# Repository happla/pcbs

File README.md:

# pcbs
## Links:
[ESP32-C3-Dev-board without  filling and gnd plane](https://github.com/happla/pcbs/tree/main/xiaobreakout) 
<br>

# enclosure

## Links : 
[ILI9341 display enclosure v1](https://github.com/happla/pcbs/tree/main/enclosure/ili9341case)
<br>

final version of ili9341 display case for iot project. V3 with m3 screw and m16x2 cable gland placeholders <br>

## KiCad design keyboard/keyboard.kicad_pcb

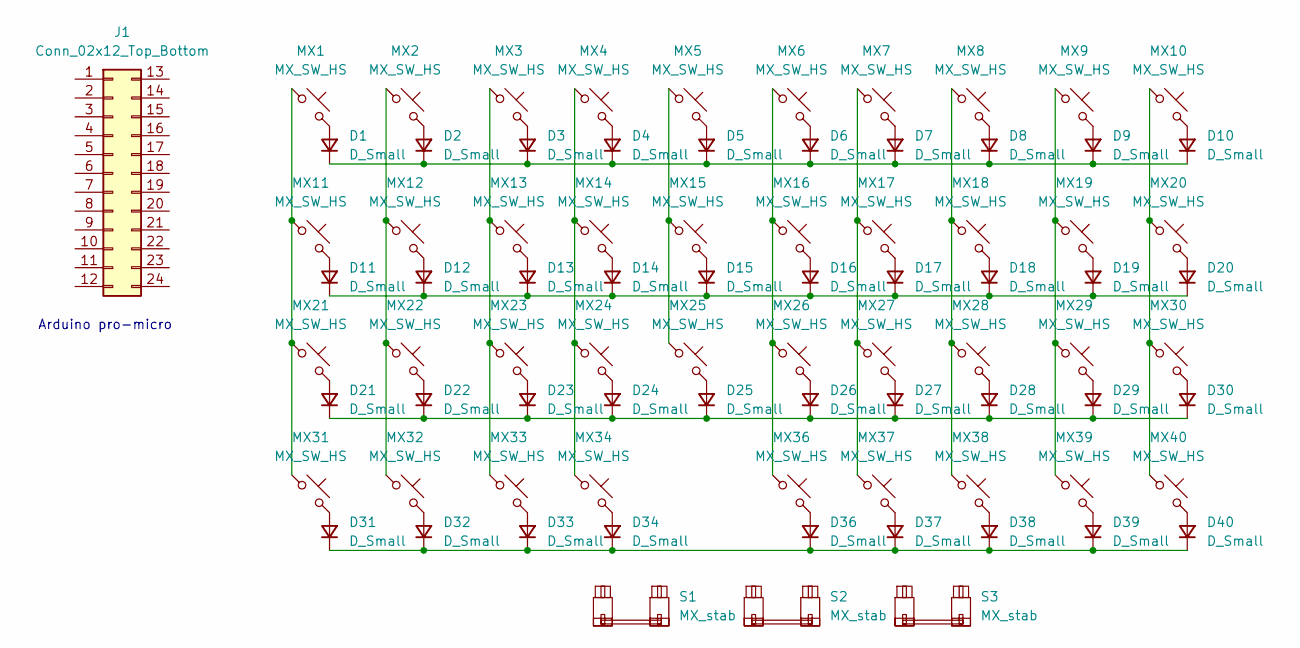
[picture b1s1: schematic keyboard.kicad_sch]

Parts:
D1, D2, D3, D4, D5, D6, D7, D8, D9, D10, D11, D12, D13, D14, D15, D16, D17, D18, D19, D20, D21, D22, D23, D24, D25, D26, D27, D28, D29, D30, D31, D32, D33, D34, D36, D37, D38, D39, D40: D_Small; D_SOD-123
J1: Conn_02x12_Top_Bottom; ProMicro_USBup
MX1, MX2, MX3, MX4, MX5, MX6, MX7, MX8, MX9, MX12, MX13, MX14, MX15, MX16, MX17, MX18, MX19, MX22, MX23, MX24, MX25, MX26, MX27, MX28, MX29, MX31, MX32, MX33, MX34, MX36, MX37, MX38, MX39: MX_SW_HS; SW_MX_1u
MX10, MX21: MX_SW_HS; SW_MX_1.75u
MX11, MX30: MX_SW_HS; SW_MX_1.25u
MX20, MX40: MX_SW_HS; SW_MX_1.5u
S1: MX_stab; STAB_MX_P_2u
S2: MX_stab; STAB_MX_P_2.25u
S3: MX_stab; STAB_MX_6.25u

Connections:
unnamed: D1.2 (A), MX1.2
unnamed: D1.1 (K), D2.1 (K), D3.1 (K), D4.1 (K), D5.1 (K), D6.1 (K), D7.1 (K), D8.1 (K), D9.1 (K), D10.1 (K)
unnamed: D2.2 (A), MX2.2
unnamed: D3.2 (A), MX3.2
unnamed: D4.2 (A), MX4.2
unnamed: D5.2 (A), MX5.2
unnamed: D6.2 (A), MX6.2
unnamed: D7.2 (A), MX7.2
unnamed: D8.2 (A), MX8.2
unnamed: D9.2 (A), MX9.2
unnamed: D10.2 (A), MX10.2
unnamed: D11.2 (A), MX11.2
unnamed: D11.1 (K), D12.1 (K), D13.1 (K), D14.1 (K), D15.1 (K), D16.1 (K), D17.1 (K), D18.1 (K), D19.1 (K), D20.1 (K)
unnamed: D12.2 (A), MX12.2
unnamed: D13.2 (A), MX13.2
unnamed: D14.2 (A), MX14.2
unnamed: D15.2 (A), MX15.2
unnamed: D16.2 (A), MX16.2
unnamed: D17.2 (A), MX17.2
unnamed: D18.2 (A), MX18.2
unnamed: D19.2 (A), MX19.2
unnamed: D20.2 (A), MX20.2
unnamed: D21.2 (A), MX21.2
unnamed: D21.1 (K), D22.1 (K), D23.1 (K), D24.1 (K), D25.1 (K), D26.1 (K), D27.1 (K), D28.1 (K), D29.1 (K), D30.1 (K)
unnamed: D22.2 (A), MX22.2
unnamed: D23.2 (A), MX23.2
unnamed: D24.2 (A), MX24.2
unnamed: D25.2 (A), MX25.2
unnamed: D26.2 (A), MX26.2
unnamed: D27.2 (A), MX27.2
unnamed: D28.2 (A), MX28.2
unnamed: D29.2 (A), MX29.2
unnamed: D30.2 (A), MX30.2
unnamed: D31.2 (A), MX31.2
unnamed: D31.1 (K), D32.1 (K), D33.1 (K), D34.1 (K), D36.1 (K), D37.1 (K), D38.1 (K), D39.1 (K), D40.1 (K)
unnamed: D32.2 (A), MX32.2
unnamed: D33.2 (A), MX33.2
unnamed: D34.2 (A), MX34.2
unnamed: D36.2 (A), MX36.2
unnamed: D37.2 (A), MX37.2
unnamed: D38.2 (A), MX38.2
unnamed: D39.2 (A), MX39.2
unnamed: D40.2 (A), MX40.2
unnamed: MX1.1, MX11.1, MX21.1, MX31.1
unnamed: MX10.1, MX20.1, MX30.1, MX40.1
unnamed: MX2.1, MX12.1, MX22.1, MX32.1
unnamed: MX3.1, MX13.1, MX23.1, MX33.1
unnamed: MX4.1, MX14.1, MX24.1, MX34.1
unnamed: MX5.1, MX15.1, MX25.1
unnamed: MX6.1, MX16.1, MX26.1, MX36.1
unnamed: MX7.1, MX17.1, MX27.1, MX37.1
unnamed: MX8.1, MX18.1, MX28.1, MX38.1
unnamed: MX9.1, MX19.1, MX29.1, MX39.1

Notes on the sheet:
Arduino pro-micro

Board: 2 copper layers, 82 parts (0 on the bottom side), 53 nets, no tracks yet.

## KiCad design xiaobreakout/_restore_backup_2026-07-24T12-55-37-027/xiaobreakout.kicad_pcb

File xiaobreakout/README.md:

# ESP32-C3 BLE Development Board

> **Status:** Work in Progress (Incomplete and untested)

A custom, ultra-compact devboard designed specifically for a Bluetooth Low Energy (BLE) project.

## Specifications

* **MCU:** ESP32-C3
* **PCB Size:** ~30 x 25 mm
* **Connectivity:** JST connectors or standard female Dupont headers

## Pin Connections

* **I2C:** [Add specific GPIOs, e.g., SDA: GPIO4, SCL: GPIO5]
* **Battery:** [Add power input details]
* **Joystick:** [Add pin mapping]
* **SW1:** [Add button pin]

## PCB Preview

## Next Steps

* [ ] Implement a circuit/method to accurately measure low-power consumption.
* [ ] Expand pin breakouts and connections for more universal prototyping use.
* [ ] Explore designing a completely scratch-built revision using an alternative MCU (like a Nordic nRF chip or CH32) to benchmark minimal power consumption.

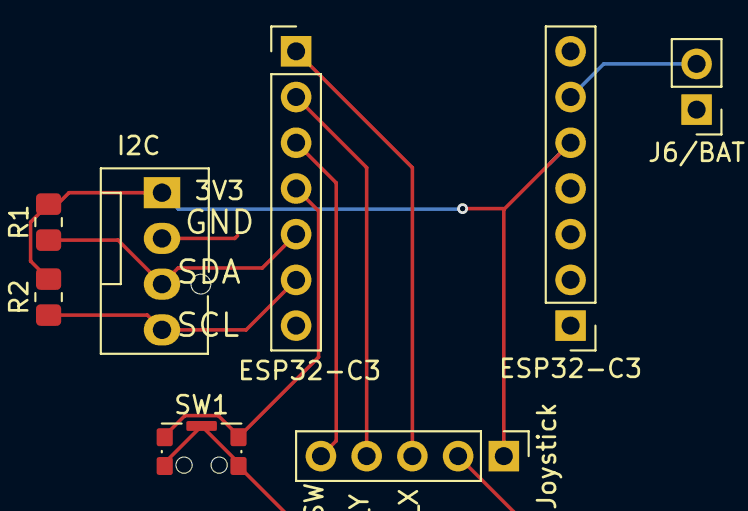
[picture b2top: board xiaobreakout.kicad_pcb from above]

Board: 2 copper layers, 8 parts (0 on the bottom side), 8 nets.

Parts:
3V3: I2C; FanPinHeader_1x04_P2.54mm_Vertical
ESP32-C3, ESP32-C3#2: Conn_01x07_Socket; PinHeader_1x07_P2.54mm_Vertical
J6/BAT: BATTERY JST connector; PinHeader_1x02_P2.54mm_Vertical
Joystick: Joystick; PinHeader_1x05_P2.54mm_Vertical
R1, R2: 4.7k; R_0805_2012Metric_Pad1.20x1.40mm_HandSolder
SW1: CK_KMS2xxG; SW_SPST_CK_KMS2xxGP

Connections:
/3V3: 3V3.1, ESP32-C3.5, Joystick.1, R1.2, R2.2
/GND: 3V3.2, ESP32-C3.6, J6/BAT.2, Joystick.2, SW1.2, SW1.SH (B)
/JOY_BACK: ESP32-C3#2.4, SW1.1
/JOY_SW: ESP32-C3#2.3, Joystick.5
/JOY_X: ESP32-C3#2.1, Joystick.3
/JOY_Y: ESP32-C3#2.2, Joystick.4
/SCL/I2C: 3V3.4, ESP32-C3#2.6, R2.1
/SDA/I2C: 3V3.3, ESP32-C3#2.5, R1.1
